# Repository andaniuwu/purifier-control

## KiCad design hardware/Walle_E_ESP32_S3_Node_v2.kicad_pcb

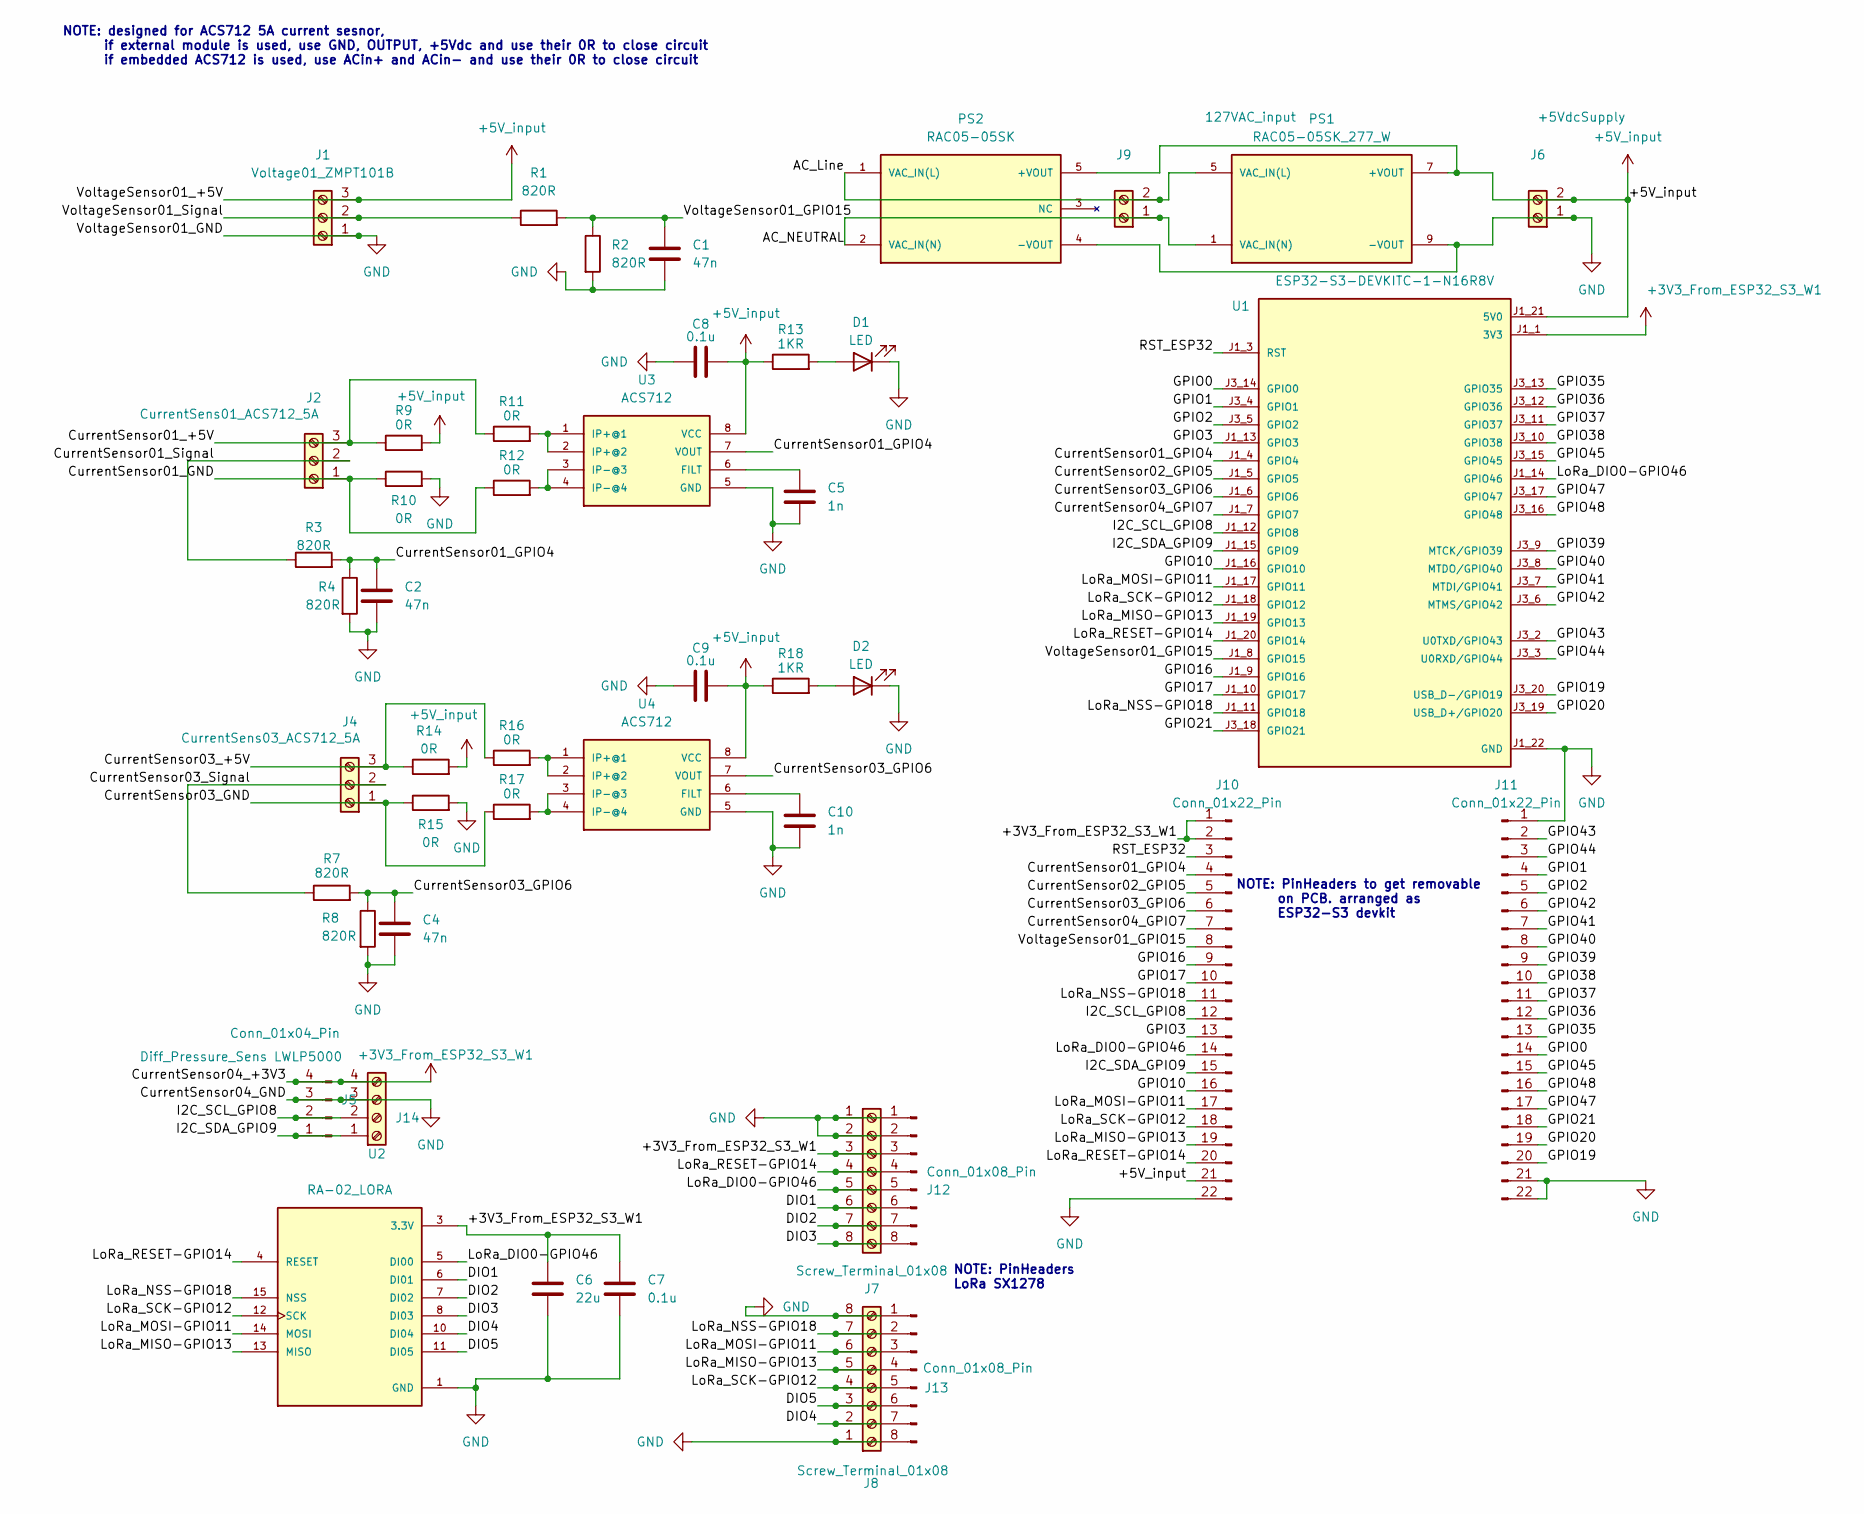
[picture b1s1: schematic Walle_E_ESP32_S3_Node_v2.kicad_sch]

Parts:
C1, C2, C4: 47n; C_Disc_D5.0mm_W2.5mm_P5.00mm
C5, C10: 1n; C_Disc_D5.0mm_W2.5mm_P5.00mm
C6: 22u; C_Disc_D5.0mm_W2.5mm_P5.00mm
C7, C8, C9: 0.1u; C_Disc_D5.0mm_W2.5mm_P5.00mm
D1, D2: LED; LED_D3.0mm
J1: Voltage01_ZMPT101B; TerminalBlock_Phoenix_MKDS-1,5-3-5.08_1x03_P5.08mm_Horizont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
J2: CurrentSens01_ACS712_5A; TerminalBlock_Phoenix_MKDS-1,5-3-5.08_1x03_P5.08mm_Horizont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
J4: CurrentSens03_ACS712_5A; TerminalBlock_Phoenix_MKDS-1,5-3-5.08_1x03_P5.08mm_Horizont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
J5: Conn_01x04_Pin; PinHeader_1x04_P2.54mm_Vertical
J6: +5VdcSupply; TerminalBlock_Phoenix_MKDS-3-2-5.08_1x02_P5.08mm_Horizontal
J7, J8: Screw_Terminal_01x08; TerminalBlock_Phoenix_MPT-0,5-8-2.54_1x08_P2.54mm_Horizontal
J9: 127VAC_input; TerminalBlock_Phoenix_MKDS-3-2-5.08_1x02_P5.08mm_Horizontal
J10, J11: Conn_01x22_Pin; PinHeader_1x22_P2.54mm_Vertical
J12, J13: Conn_01x08_Pin; PinHeader_1x08_P2.54mm_Vertical
J14: Diff_Pressure_Sens LWLP5000; TerminalBlock_Phoenix_MKDS-3-4-5.08_1x04_P5.08mm_Horizontal
PS1: RAC05-05SK_277_W; CONV_RAC05-05SK_277_W; PARTREV N/A
PS2: RAC05-05SK; CONV_RAC05-05SK; PARTREV 7
R1, R2, R3, R4, R7, R8: 820R; R_Axial_DIN0411_L9.9mm_D3.6mm_P12.70mm_Horizontal
R9, R10, R11, R12, R14, R15, R16, R17: 0R; R_Axial_DIN0411_L9.9mm_D3.6mm_P12.70mm_Horizontal
R13, R18: 1KR; R_Axial_DIN0411_L9.9mm_D3.6mm_P12.70mm_Horizontal
U1: ESP32-S3-DEVKITC-1-N16R8V; XCVR_ESP32-S3-DEVKITC-1-N16R8V; PARTREV 1.1
U2: RA-02_LORA; MODULE_RA-02_LORA; PARTREV 2018/03/02
U3, U4: ACS712; SO08

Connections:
+3V3_From_ESP32_S3_W1: C6.1, C7.1, J5.4, J7.3, J10.1, J10.2, J12.3, J14.4, U1.J1_1 (3V3), U1.J1_2 (3V3), U2.3 (3.3V)
+5V_input: C8.2, C9.2, J1.3, J6.2, J10.21, PS1.7 (+VOUT), PS2.5 (+VOUT), R9.2, R13.1, R14.2, R18.1, U1.J1_21 (5V0), U3.8 (VCC), U4.8 (VCC)
/AC_Line: J9.2, PS1.5 (VAC_IN(L)), PS2.1 (VAC_IN(L))
/AC_NEUTRAL: J9.1, PS1.1 (VAC_IN(N)), PS2.2 (VAC_IN(N))
/CurrentSensor01_+5V: J2.3, R9.1, R11.1
/CurrentSensor01_GND: J2.1, R10.1, R12.1
/CurrentSensor01_GPIO4: C2.1, J10.4, R3.2, R4.1, U1.J1_4 (GPIO4), U3.7 (VOUT)
/CurrentSensor01_Signal: J2.2, R3.1
/CurrentSensor02_GPIO5: J10.5, U1.J1_5 (GPIO5)
/CurrentSensor03_+5V: J4.3, R14.1, R16.1
/CurrentSensor03_GND: J4.1, R15.1, R17.1
/CurrentSensor03_GPIO6: C4.1, J10.6, R7.2, R8.1, U1.J1_6 (GPIO6), U4.7 (VOUT)
/CurrentSensor03_Signal: J4.2, R7.1
/CurrentSensor04_GPIO7: J10.7, U1.J1_7 (GPIO7)
/DIO1: J7.6, J12.6, U2.6 (DI01)
/DIO2: J7.7, J12.7, U2.7 (DI02)
/DIO3: J7.8, J12.8, U2.8 (DI03)
/DIO4: J8.2, J13.7, U2.10 (DI04)
/DIO5: J8.3, J13.6, U2.11 (DI05)
/GPIO0: J11.14, U1.J3_14 (GPIO0)
/GPIO1: J11.4, U1.J3_4 (GPIO1)
/GPIO2: J11.5, U1.J3_5 (GPIO2)
/GPIO3: J10.13, U1.J1_13 (GPIO3)
/GPIO10: J10.16, U1.J1_16 (GPIO10)
/GPIO16: J10.9, U1.J1_9 (GPIO16)
/GPIO17: J10.10, U1.J1_10 (GPIO17)
/GPIO19: J11.20, U1.J3_20 (USB_D-/GPIO19)
/GPIO20: J11.19, U1.J3_19 (USB_D+/GPIO20)
/GPIO21: J11.18, U1.J3_18 (GPIO21)
/GPIO35: J11.13, U1.J3_13 (GPIO35)
/GPIO36: J11.12, U1.J3_12 (GPIO36)
/GPIO37: J11.11, U1.J3_11 (GPIO37)
/GPIO38: J11.10, U1.J3_10 (GPIO38)
/GPIO39: J11.9, U1.J3_9 (MTCK/GPIO39)
/GPIO40: J11.8, U1.J3_8 (MTDO/GPIO40)
/GPIO41: J11.7, U1.J3_7 (MTDI/GPIO41)
/GPIO42: J11.6, U1.J3_6 (MTMS/GPIO42)
/GPIO43: J11.2, U1.J3_2 (U0TXD/GPIO43)
/GPIO44: J11.3, U1.J3_3 (U0RXD/GPIO44)
/GPIO45: J11.15, U1.J3_15 (GPIO45)
/GPIO47: J11.17, U1.J3_17 (GPIO47)
/GPIO48: J11.16, U1.J3_16 (GPIO48)
/I2C_SCL_GPIO8: J5.2, J10.12, J14.2, U1.J1_12 (GPIO8)
/I2C_SDA_GPIO9: J5.1, J10.15, J14.1, U1.J1_15 (GPIO9)
/LoRa_DIO0-GPIO46: J7.5, J10.14, J12.5, U1.J1_14 (GPIO46), U2.5 (DI00)
/LoRa_MISO-GPIO13: J8.5, J10.19, J13.4, U1.J1_19 (GPIO13), U2.13 (MISO)
/LoRa_MOSI-GPIO11: J8.6, J10.17, J13.3, U1.J1_17 (GPIO11), U2.14 (MOSI)
/LoRa_NSS-GPIO18: J8.7, J10.11, J13.2, U1.J1_11 (GPIO18), U2.15 (NSS)
/LoRa_RESET-GPIO14: J7.4, J10.20, J12.4, U1.J1_20 (GPIO14), U2.4 (RESET)
/LoRa_SCK-GPIO12: J8.4, J10.18, J13.5, U1.J1_18 (GPIO12), U2.12 (SCK)
/RST_ESP32: J10.3, U1.J1_3 (RST)
/VoltageSensor01_GPIO15: C1.1, J10.8, R1.2, R2.1, U1.J1_8 (GPIO15)
/VoltageSensor01_Signal: J1.2, R1.1
GND: C1.2, C2.2, C4.2, C5.2, C6.2, C7.2, C8.1, C9.1, C10.2, D1.1 (K), D2.1 (K), J1.1, J5.3, J6.1, J7.1, J7.2, J8.1, J8.8, J10.22, J11.1, J11.21, J11.22, J12.1, J12.2, J13.1, J13.8, J14.3, PS1.9 (-VOUT), PS2.4 (-VOUT), R2.2, R4.2, R8.2, R10.2, R15.2, U1.J1_22 (GND), U1.J3_1 (GND), U1.J3_21 (GND), U1.J3_22 (GND), U2.1 (GND), U2.2 (GND), U2.9 (GND), U2.16 (GND), U3.5 (GND), U4.5 (GND)
unnamed: D1.2 (A), R13.2
unnamed: D2.2 (A), R18.2
unnamed: C5.1, U3.6 (FILT)
unnamed: R11.2, U3.1 (IP+@1), U3.2 (IP+@2)
unnamed: R12.2, U3.3 (IP-@3), U3.4 (IP-@4)
unnamed: C10.1, U4.6 (FILT)
unnamed: R16.2, U4.1 (IP+@1), U4.2 (IP+@2)
unnamed: R17.2, U4.3 (IP-@3), U4.4 (IP-@4)

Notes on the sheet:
NOTE: designed for ACS712 5A current sesnor, if external module is used, use GND, OUTPUT, +5Vdc and use their 0R to close circuit if embedded ACS712 is used, use ACin+ and ACin- and use their 0R to close circuit
NOTE: PinHeaders to get removable on PCB. arranged as ESP32-S3 devkit
NOTE: PinHeaders LoRa SX1278

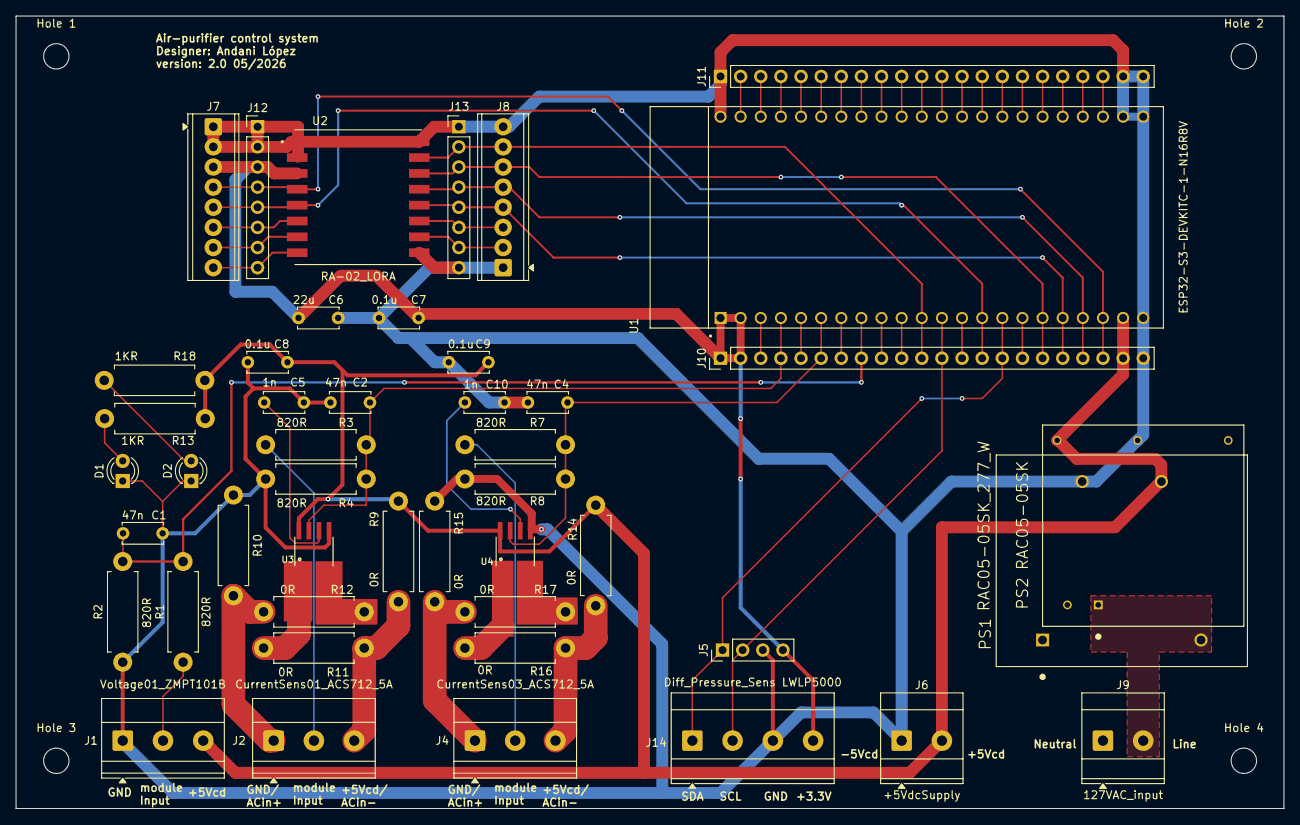
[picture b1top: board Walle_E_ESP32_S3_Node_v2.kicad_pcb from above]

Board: 2 copper layers, 160.0 x 100.0 mm, 50 parts (0 on the bottom side), 62 nets.

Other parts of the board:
Hole 1, Hole 2, Hole 3, Hole 4: MountingHole_3.2mm_M3

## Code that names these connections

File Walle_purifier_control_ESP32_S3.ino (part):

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// los números de GPIO y no la función SPI fija. La asignación se realiza así:
//   SPI.begin(SCK, MISO, MOSI, SS);
// En este proyecto:
//   SCK  = GPIO12 (Pin 19, FSPI_CLK)
//   MISO = GPIO13 (Pin 18, FSPI_Q)
//   MOSI = GPIO11 (Pin 17, FSPI_D)
//   NSS  = GPIO18 (Pin 9)
//   RESET= GPIO14 (Pin 13)
//   DIO0 = GPIO26 (Pin 38)
// ----------------------------------------------------------------------------------
// Tabla de conexión SX1278 ↔ ESP32-S3-DevKitC-1:
// SX1278 Pin | ESP32 GPIO | ESP32 Pin# | Función en código
// -----------|------------|------------|------------------
// SCK        | GPIO12     | Pin 19     | SPI SCK
// MISO       | GPIO13     | Pin 18     | SPI MISO
// MOSI       | GPIO11     | Pin 17     | SPI MOSI
// NSS (CS)   | GPIO18     | Pin 9      | LORA_SS
// RESET      | GPIO14     | Pin 13     | LORA_RST
// DIO0       | GPIO46     | Pin 44     | LORA_DIO0
// 3.3V       | 3V3        | Pin 2/3    | Alimentación
// GND        | GND        | Pin 1/15/16| Tierra
// ----------------------------------------------------------------------------------
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// ─────────────────────────────────────────────────────────────────────────

// ---- ADC Sensor Pins (ESP32-S3 ADC1 channels) ----
// Valid ADC1 pins on ESP32-S3: GPIO0-8, GPIO14-15
#define CURRENT_SENSOR1 4     // GPIO4 (ADC1_CH3) - ACS712T-5A Channel 1
#define CURRENT_SENSOR2 5     // GPIO5 (ADC1_CH4) - ACS712T-5A Channel 2
#define CURRENT_SENSOR3 6     // GPIO6 (ADC1_CH5) - ACS712T-5A Channel 3
#define CURRENT_SENSOR4 7     // GPIO7 (ADC1_CH6) - ACS712T-5A Channel 4
#define AC_POWER_PIN    15    // GPIO15 (ADC1_CH14) - AC voltage detector (ZMPT101B)

// ---- LoRa Module Pins (SX1278/RFM95) ----
#define LORA_SCK        12    // GPIO12 (Pin 19)
#define LORA_MISO       13    // GPIO13 (Pin 18)
#define LORA_MOSI       11    // GPIO11 (Pin 17)
#define LORA_SS         18    // GPIO18 (Pin 9)
#define LORA_RST        14    // GPIO14 (Pin 13)
#define LORA_DIO0       46    // GPIO46 (Pin 44)

// ---- LoRa RF profile (robust mode for noisy industrial environments) ----
#define LORA_FREQUENCY_HZ    433E6
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#define LORA_TX_POWER_DBM    17       // Safe high power for SX1278 modules

// ---- Indicator LED ----
#define LED_PIN         2     // Onboard LED (GPIO2) - indicates system running

// ---- Tower light relay outputs ----
// GPIO16 and GPIO17 are free digital GPIOs on the ESP32-S3-WROOM-1 DevKitC-1.
// The internal flash/PSRAM on WROOM-1 uses GPIO26-32 (SPI0), so 16 and 17 are safe.
// They don't interfere with ADC1 channels (GPIO0-8 used there), boot strapping, or USB.
//
// Wiring: connect each output to IN pin of your optocoupler relay board.
//   GREEN relay → K1 → turns ON the green tower light  (lamps OK)
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//   true  = relay energizes when GPIO drives HIGH (standard optocoupler boards with
//           on-board flyback and INPUT tied to 3.3 V logic via 1k resistor).
//   false = relay energizes when GPIO drives LOW  (active-LOW boards, less common).
#define TOWER_RELAY_GREEN_PIN   16    // GPIO16 → relay K1 (green light)
#define TOWER_RELAY_RED_PIN     17    // GPIO17 → relay K2 (red light)
#define TOWER_RELAY_ACTIVE_HIGH false // Active-LOW relay board (LOW energizes coil)

// ---- I2C Bus – reserved for future OLED display and pressure sensor ----
// Both devices share the same I2C bus (Wire).  Call Wire.begin(I2C_SDA_PIN, I2C_SCL_PIN)
// once in setup() when those peripherals are added.
//
// GPIO8 / GPIO9 are the ESP32-S3 Arduino-core default SDA/SCL pins and are free here.
//
// Device addresses (7-bit, as used by Arduino Wire):
//   OLED SSD1306 128×64 :  0x3C  (= 0x78 in 8-bit datasheet notation >> 1)
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//   The LWLP5000 chip uses I2C address 0x00 (confirmed in DFRobot official example).
//   This is an unusually low address – do NOT confuse it with the I2C general-call
//   address (also 0x00 in some specs).  The DFRobot_LWLP library handles it correctly.
#define I2C_SDA_PIN          9     // GPIO9  – Wire SDA (OLED + pressure sensor)
#define I2C_SCL_PIN          8     // GPIO8  – Wire SCL (OLED + pressure sensor)
#define OLED_I2C_ADDR        0x3C  // SSD1306 7-bit address  (datasheet shows 0x78 = 8-bit)
#define PRESSURE_I2C_ADDR    0x00  // SEN0343 LWLP5000 7-bit address (fixed, per DFRobot)

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// To reverse a motor swap the HIGH/LOW on its pair (IN1/IN2 or IN3/IN4).
// To brake a motor set both pins of a pair to the SAME level (both HIGH or both LOW).
//
// GPIO35-38 are safe on WROOM-1: not strapping pins, not internal-flash SPI, not USB.
#define L298N_IN1  35   // GPIO35 → L298N IN1  (Motor A +)
#define L298N_IN2  36   // GPIO36 → L298N IN2  (Motor A -)
#define L298N_IN3  37   // GPIO37 → L298N IN3  (Motor B +)
#define L298N_IN4  38   // GPIO38 → L298N IN4  (Motor B -)
#define L298N_ENA  39   // GPIO39 → L298N ENA  (Motor A enable – PWM)
#define L298N_ENB  40   // GPIO40 → L298N ENB  (Motor B enable – PWM)

// PWM configuration for ENA/ENB (100% duty = máxima potencia constante)
// Frecuencia 1 kHz: suficiente para el L298N, sin ruido audible apreciable.
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#define L298N_PWM_DUTY  255    // 100% – máxima potencia

// WS2812 RGB LED (NeoPixel) configuration
#define NEOPIXEL_PIN    48    // GPIO48 for WS2812 addressable RGB LED
#define NEOPIXEL_COUNT  1     // Single LED on most DevKits
Adafruit_NeoPixel neopixel(NEOPIXEL_COUNT, NEOPIXEL_PIN, NEO_GRB + NEO_KHZ800);

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#define COLOR_WHITE     neopixel.Color(255, 255, 255)
#define COLOR_PURPLE    neopixel.Color(128, 0, 128)

// OLED SSD1306 128x64 display object (I2C via GPIO8=SDA, GPIO9=SCL)
Adafruit_SSD1306 display(128, 64, &Wire, -1);


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
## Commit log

2026-05-14 Initial commit: ESP32-S3 LoRa UV purifier control
2026-05-18 Swap I2C pins: SDA→GPIO9, SCL→GPIO8
2026-05-21 Add KiCad PCB project (v2) and Gerber files
2026-05-21 Add custom KiCad libraries (ACS712, ESP32-S3, RA-02 LoRa, power supply)
2026-05-21 Thickness improve in AC current sensor input AC line
2026-05-25 AC line corrections: trace width, routing improvements and Gerber update
